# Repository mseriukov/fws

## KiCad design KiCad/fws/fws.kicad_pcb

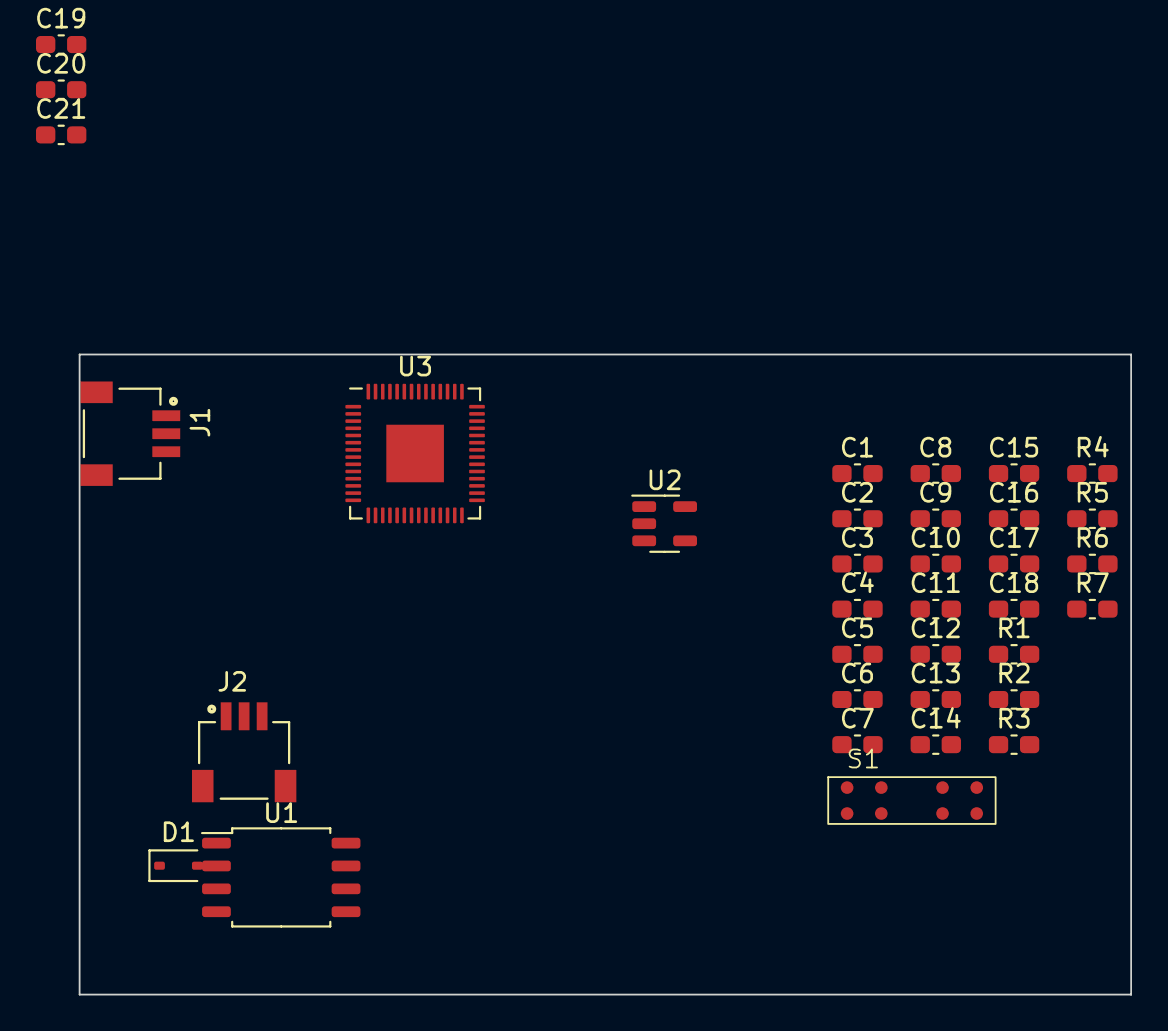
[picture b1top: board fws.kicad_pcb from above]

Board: 2 copper layers, 58.4 x 35.6 mm, 35 parts (0 on the bottom side), 25 nets, no tracks yet.

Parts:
C1, C8, C10, C13, C14, C15, C16, C18, C20, C21: 100nF; C_0603_1608Metric_Pad1.08x0.95mm_HandSolder
C2, C6, C11, C12: 4.7uF; C_0603_1608Metric_Pad1.08x0.95mm_HandSolder
C3, C9: 10uF; C_0603_1608Metric_Pad1.08x0.95mm_HandSolder
C4, C5: 27pF; C_0603_1608Metric_Pad1.08x0.95mm_HandSolder
C7: 470pF; C_0603_1608Metric_Pad1.08x0.95mm_HandSolder
C17: 100n; C_0603_1608Metric_Pad1.08x0.95mm_HandSolder
C19: 22uF; C_0603_1608Metric_Pad1.08x0.95mm_HandSolder
D1: 1N5819WS; D_SOD-323
J1: JST_SM03B-SRSS-TB_LF__SN_; SM03B-SRSS-TB_LF__SN_
J2: SM03B-SRSS-TB_LF__SN_
R1: 1K; C_0603_1608Metric_Pad1.08x0.95mm_HandSolder
R2, R5: 10K; C_0603_1608Metric_Pad1.08x0.95mm_HandSolder
R3, R4: R; C_0603_1608Metric_Pad1.08x0.95mm_HandSolder
R6, R7: 27R; C_0603_1608Metric_Pad1.08x0.95mm_HandSolder
S1: s13131-1536
U1: W25Q128JVS; SOIC-8_5.23x5.23mm_P1.27mm
U2: MIC5205-3.3YM5; SOT-23-5
U3: RP2040; QFN-56-1EP_7x7mm_P0.4mm_EP3.2x3.2mm

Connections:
+1V1: C6.1, C8.1, C10.1, U3.23 (DVDD), U3.45 (VREG_VOUT), U3.50 (DVDD)
+3.3V: C1.1, C9.1, C12.1, C13.1, C14.1, C15.1, C16.1, C17.1, C18.1, C19.1, C20.1, C21.1, R2.1, R5.1, S1.6 (Vdd), U1.8 (VCC), U2.5 (OUT), U3.1 (IOVDD), U3.10 (IOVDD), U3.22 (IOVDD), U3.33 (IOVDD), U3.42 (IOVDD), U3.43 (ADC_AVDD), U3.44 (VREG_IN), U3.48 (USB_VDD), U3.49 (IOVDD)
/CLK: S1.1 (CLK), U3.37 (GPIO25)
/EOS: S1.5 (EOS), U3.34 (GPIO22)
/QSPI_SCLK: U1.6 (CLK), U3.52 (QSPI_SCLK)
/QSPI_SD0: U1.5 (DI(IO0)), U3.53 (QSPI_SD0)
/QSPI_SD1: U1.2 (DO(IO1)), U3.55 (QSPI_SD1)
/QSPI_SD2: U1.3 (IO2), U3.54 (QSPI_SD2)
/QSPI_SD3: U1.7 (IO3), U3.51 (QSPI_SD3)
/QSPI_SS: R1.2, R2.2, U1.1 (~CS), U3.56 (QSPI_SS)
/ST: S1.8 (ST), U3.36 (GPIO24)
/SWCLK: J2.1, U3.24 (SWCLK)
/SWD: J2.3, U3.25 (SWD)
/TRIG: S1.7 (Trig), U3.35 (GPIO23)
/VIDEO: S1.4 (Video), U3.38 (GPIO26_ADC0)
GND: C1.2, C2.2, C3.2, C4.1, C5.1, C6.2, C7.2, C8.2, C9.2, C10.2, C11.2, C12.2, C13.2, C14.2, C15.2, C16.2, C17.2, C18.2, C19.2, C20.2, C21.2, J2.2, J2.S1 (SHIELD), J2.S2 (SHIELD), R3.2, R4.2, S1.3 (GND), U1.4 (GND), U2.2 (GND), U3.19 (TESTEN), U3.57 (GND)
unnamed: J1.S1 (SHIELD), J1.S2 (SHIELD)
unnamed: C11.1, S1.2 (Vcp)
unnamed: C7.1, U2.4 (BP)
unnamed: R5.2, U3.26 (RUN)
unnamed: R7.2, U3.46 (USB_DM)
unnamed: R6.1, U3.47 (USB_DP)
unnamed: C4.2, U3.20 (XIN)
unnamed: C5.2, U3.21 (XOUT)
VSYS: C2.1, C3.1, U2.1 (IN), U2.3 (EN)

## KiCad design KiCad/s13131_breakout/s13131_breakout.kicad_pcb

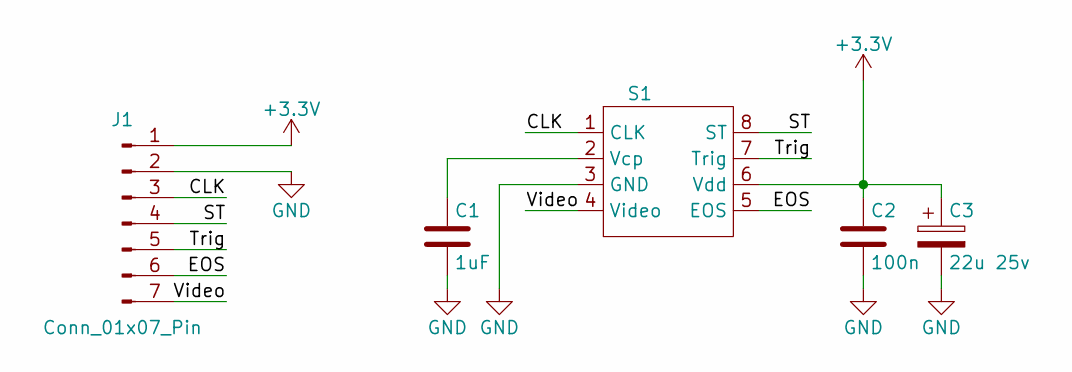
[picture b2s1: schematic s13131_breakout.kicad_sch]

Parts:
C1: 1uF; C_0805_2012Metric
C2: 100n; C_0805_2012Metric
C3: 22u 25v; CP_EIA-7343-15_Kemet-W_Pad2.25x2.55mm_HandSolder
J1: Conn_01x07_Pin; PinHeader_1x07_P2.54mm_Vertical
S1: s13131-1536

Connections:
+3.3V: C2.1, C3.1, J1.1, S1.6 (Vdd)
/CLK: J1.3, S1.1 (CLK)
/EOS: J1.6, S1.5 (EOS)
/ST: J1.4, S1.8 (ST)
/Trig: J1.5, S1.7 (Trig)
/Video: J1.7, S1.4 (Video)
GND: C1.2, C2.2, C3.2, J1.2, S1.3 (GND)
unnamed: C1.1, S1.2 (Vcp)

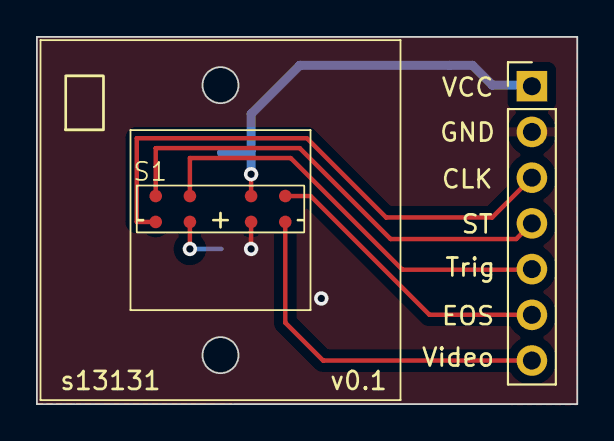
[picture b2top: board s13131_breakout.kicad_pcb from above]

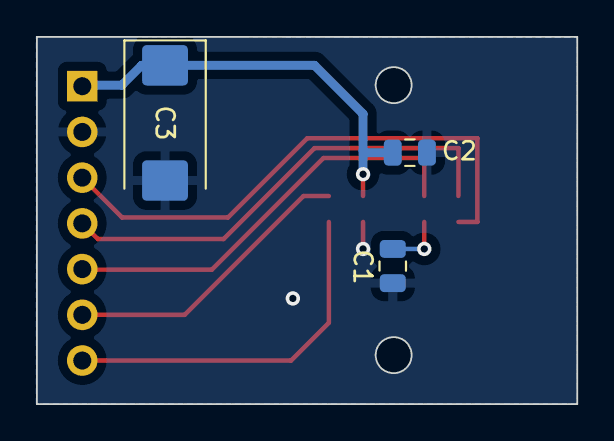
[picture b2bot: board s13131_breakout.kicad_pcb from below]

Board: 2 copper layers, 30.0 x 20.4 mm, 5 parts (3 on the bottom side), 8 nets.

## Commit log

2023-10-26 Added empty KiCad project.
2023-10-26 Added RP2040.
2023-10-26 Updated schematic.
2023-10-26 Updated schematics.
2023-10-27 Various kicad project updates.
2023-10-28 Updated 3d model for JST-SM03B.
2023-10-28 Added power and usbc.
2023-10-28 Added flash.
2023-10-28 Added clock.
2023-10-30 Started drawing s13131 footprint.
2023-10-31 Added s13131 breakout kicad project.
2023-11-01 Added demo usb project.
2023-11-02 Switched from uvc to cdc class.
2023-11-03 Minor update.
2023-11-04 Updated breakout.
2023-11-05 Added empty mac app.
2023-11-05 Removed unused test code.
2023-11-06 Added a type for serial communication.
2023-11-07 Updated formatting.
2023-11-08 Removed unused file.
2023-11-08 Unignore .vscode.
2023-11-09 Updated config.
2023-11-11 Updated breakout pcb.
2023-11-13 Updated breakout board.
2023-11-18 Updated breakout schematics.
2023-11-22 Updated breakout board and schematic.
2023-11-27 Sent breakout v0.1 to production.
2023-11-29 Updated fws schematics.
2023-12-09 Updated pcb.
2023-12-19 Updated circuit.
2024-01-07 Updated schematics
2024-01-10 Updated PCB
